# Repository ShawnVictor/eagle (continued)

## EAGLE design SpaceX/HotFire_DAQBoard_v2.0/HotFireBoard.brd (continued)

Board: 2 copper layers, 264 parts (154 on the bottom side), 219 nets, no tracks yet.

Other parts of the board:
C2, C3, C7, C10: 0.1uF; 0805
C5, C6: 47uF; PANASONIC_D
C9: 4.7uF; 0805
CONN1: USB; PN61729
D2: SOD-123
IC1: ATMEGA640-16AI; TQFP100
IC3: 7806DT; TO252
ICSP: FEMALE 2x3; 2X3
LED1: GREEN; CHIPLED_0805
LED2: YELLOW; CHIPLED_0805
LED3: BLUE; CHIPLED_0805
LED4: RED; CHIPLED_0805
R4, R5: 1k; 0805
R6, R7: 10k; 0805
R8, R9: 680; 0805
S1: DTSM-6
U$1: RESONATORSMD; RESONATOR-SMD

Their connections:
ARD_SOL1_WSV_2: IC1.42; also elsewhere on the board
ARD_SOL2_NV_2: IC1.41; also elsewhere on the board
ARD_SOL3_OV_4: IC1.40; also elsewhere on the board
ARD_SOL5: IC1.38; also elsewhere on the board
D0/RX0: IC1.2; also elsewhere on the board
D1/TX0: IC1.3; also elsewhere on the board
D+: CONN1.3; also elsewhere on the board
D-: CONN1.2; also elsewhere on the board
ETHERNET11: IC1.23, R5.2
LOADCELL_1_DOUT: IC1.5; also elsewhere on the board
LOADCELL_1_SCK: IC1.15; also elsewhere on the board
LOADCELL_2_DOUT: IC1.1; also elsewhere on the board
LOADCELL_2_SCK: IC1.16; also elsewhere on the board
LS1: IC1.58; also elsewhere on the board
LS2: IC1.57; also elsewhere on the board
LS3: IC1.56; also elsewhere on the board
LS4: IC1.55; also elsewhere on the board
LS5: IC1.54; also elsewhere on the board
MISO: IC1.22, ICSP.1; also elsewhere on the board
MOSI: IC1.21, ICSP.4; also elsewhere on the board
unnamed: LED1.A, R4.1
unnamed: LED2.A, R5.1
unnamed: LED3.C, R8.1
unnamed 103: R9.2; also elsewhere on the board
unnamed 104: R8.2; also elsewhere on the board
unnamed: LED4.C, R9.1
SCK: IC1.20, ICSP.3; also elsewhere on the board
SCL: IC1.43, R6.1; also elsewhere on the board
SDA: IC1.44, R7.1; also elsewhere on the board
TC1_CS: IC1.71; also elsewhere on the board
TC2_CS: IC1.72; also elsewhere on the board
TC3_CS: IC1.73; also elsewhere on the board
TC4_CS: IC1.74; also elsewhere on the board
TC5_CS: IC1.75; also elsewhere on the board
TC6_CS: IC1.76; also elsewhere on the board
TC7_CS: IC1.77; also elsewhere on the board
TC8_CS: IC1.78; also elsewhere on the board
TC9_CS: IC1.60; also elsewhere on the board
TC10_CS: IC1.59; also elsewhere on the board
TC_DO: IC1.26; also elsewhere on the board
TC_SCK: IC1.25; also elsewhere on the board
VIN: C5.+, IC3.1; also elsewhere on the board
VUSB: C9.2, C10.2, CONN1.1, D2.A
XTAL1: IC1.34; also elsewhere on the board

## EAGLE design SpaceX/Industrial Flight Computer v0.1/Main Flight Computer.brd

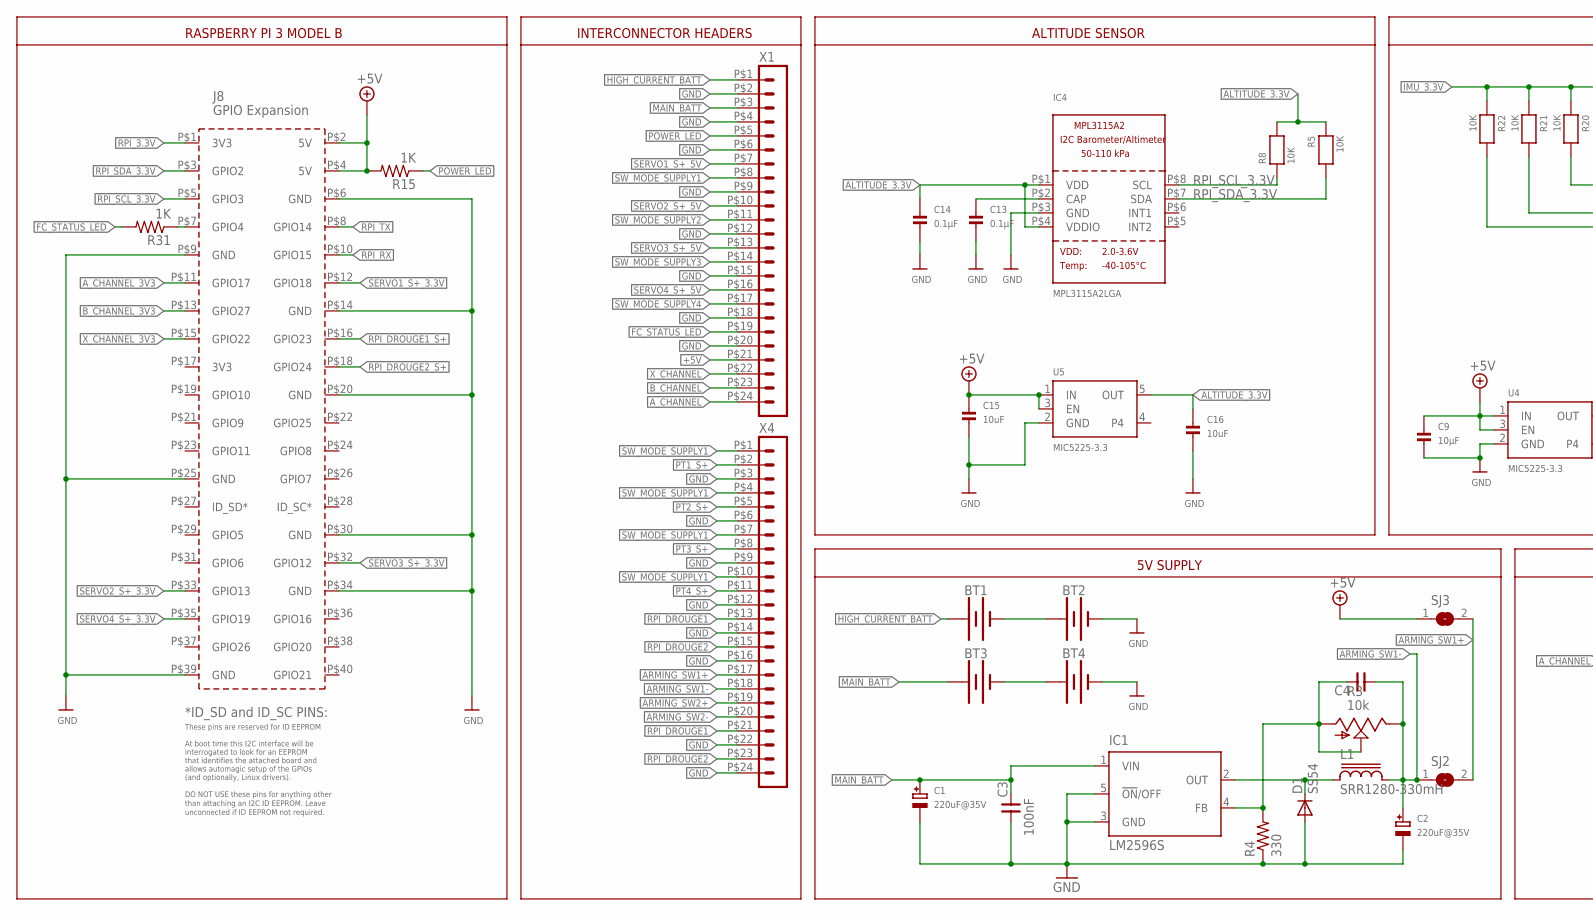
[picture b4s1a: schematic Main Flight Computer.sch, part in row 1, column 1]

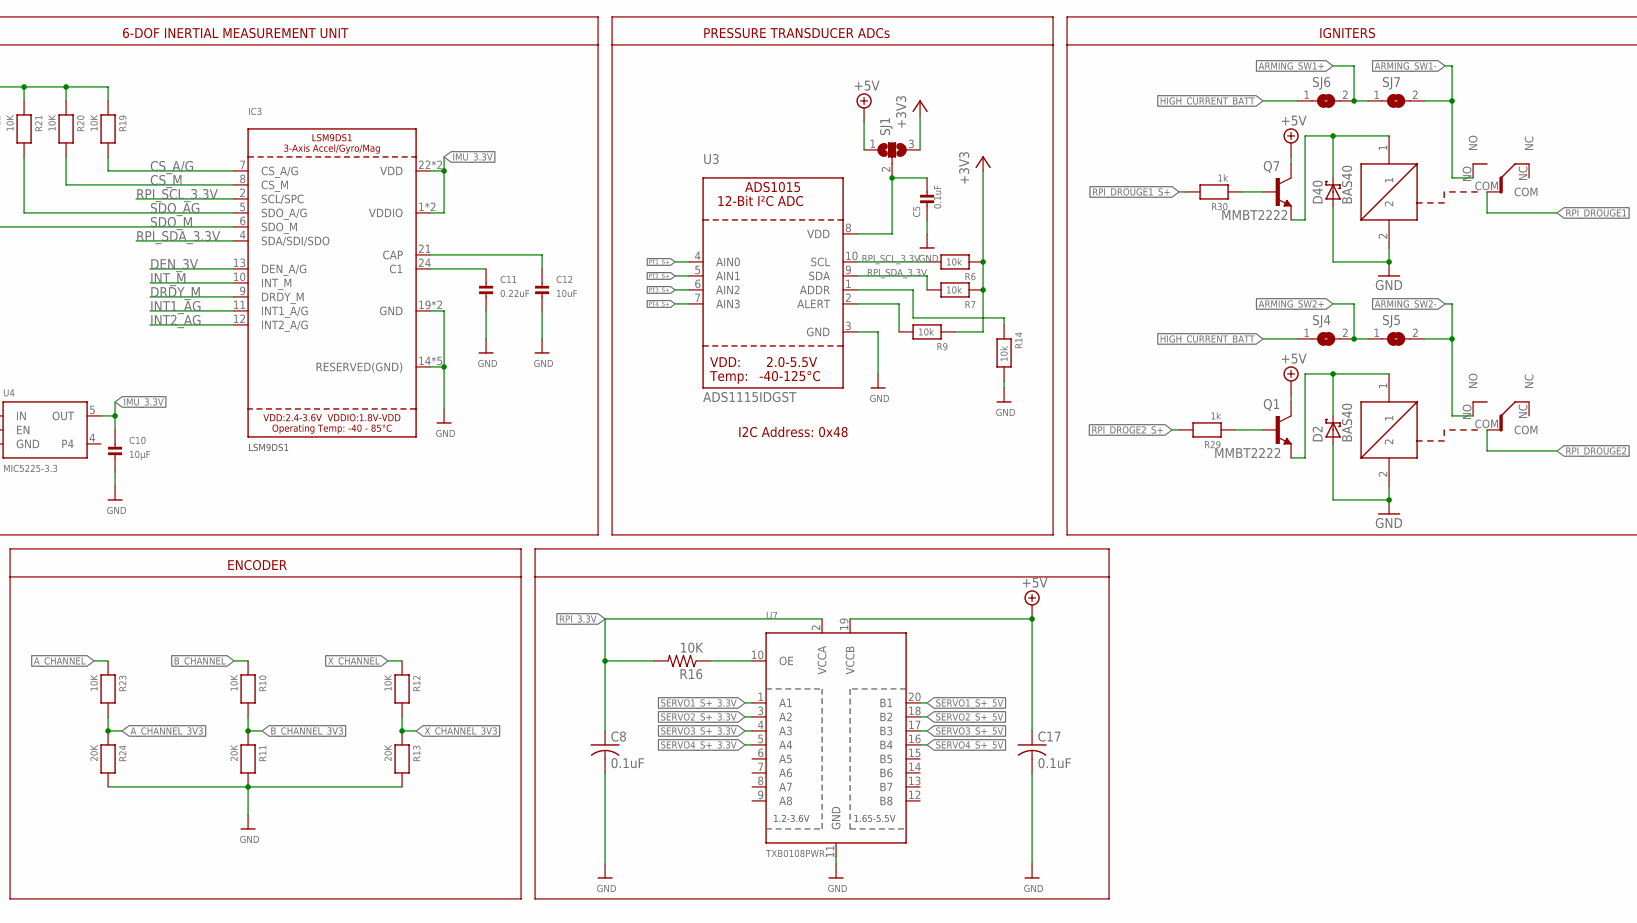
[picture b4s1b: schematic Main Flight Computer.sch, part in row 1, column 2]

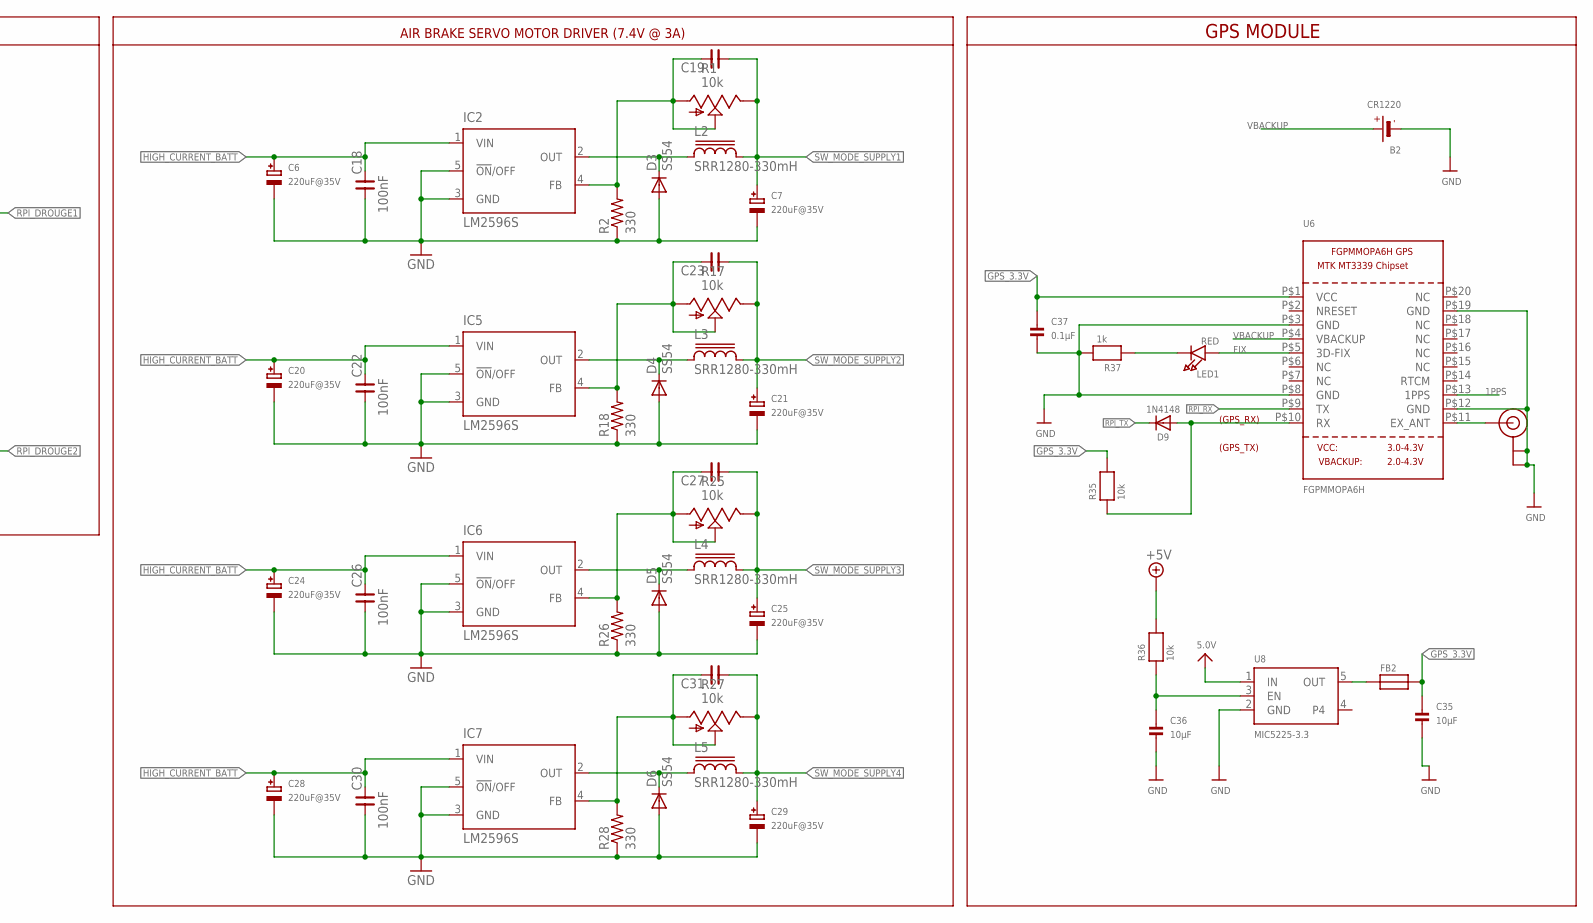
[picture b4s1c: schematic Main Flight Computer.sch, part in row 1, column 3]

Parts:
B2: CR1220
BT1, BT2, BT3, BT4: BATTERY-18650; BATTERY_18650-HOLDER
C1, C2, C6, C7, C20, C21, C24, C25, C28, C29: 220uF@35V; PANASONIC_D
C3, C18, C22, C26, C30: 100nF; 0603
C4, C19, C23, C27, C31: CNP-0603; 0603
C5: 0.1uF; 0805
C8, C17: 0.1uF; C0805
C9, C10, C35, C36: 10µF; 0603
C11: 0.22uF; 0603
C12, C15, C16: 10uF; 0603
C13, C14, C37: 0.1µF; 0603
D1, D3, D4, D5, D6: SS54; DO214AB
D2, D40: BAS40; SOT23
D9: 1N4148; SOD-323
FB2: FERRITE; 0603
IC1, IC2, IC5, IC6, IC7: LM2596S; TO263-5
IC3: LSM9DS1; LGA24_3.5X3.1MM
IC4: MPL3115A2LGA; LGA8
L1, L2, L3, L4, L5: SRR1280-330mH; SRR1280
LED1: RED; CHIPLED_0805
PCB1: RPI3
Q1, Q7: MMBT2222; SOT223
R1, R3, R17, R25, R27: 10k; S64W
R2, R4, R18, R26, R28: 330; R0603
R5, R8, R10, R12, R19, R20, R21, R22, R23: 10K; 0603
R6, R7, R9, R14: 10k; 0805
R11, R13, R24: 20K; 0603
R15, R31: 1K; R0603
R16: 10K; R0805
R29, R30, R37: 1k; 0603
R35, R36: 10k; 0603
SJ1: SJ2W; SJ_2
SJ2, SJ3, SJ4, SJ5, SJ6, SJ7: SJ
U3: ADS1115IDGST; MSOP10
U4, U5, U8: MIC5225-3.3; SOT23-5
U6: FGPMMOPA6H
U7: TXB0108PWR; TSSOP20
U$2: U.FL
U$11, U$13: RW-SH
X1, X4: HEADER_POS24_44914-2401; 44914-2401

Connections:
1PPS: U6.P$13 (1PPS)
5.0V: U8.1 (IN)
+3V3: R6.1, R7.1, R9.1, SJ1.3
+5V: C9.1, C15.1, C17.1, PCB1.P$2 (5V), PCB1.P$4 (5V), Q1.2 (C), Q7.2 (C), R15.2, R36.2, SJ1.1, SJ3.1, U4.1 (IN), U4.3 (EN), U5.1 (IN), U5.3 (EN), U7.19 (VCCB), X1.P$21 (21)
ALTITUDE_3.3V: C14.1, C16.1, IC4.P$1 (VDD), IC4.P$4 (VDDIO), R5.1, R8.2, U5.5 (OUT)
ARMING_SW1+: SJ2.2, SJ3.2, SJ6.2, SJ7.1, X4.P$17 (17)
ARMING_SW1-: C2.+, C4.1, L1.2, R3.E, SJ2.1, SJ7.2, U$11.NO, X4.P$18 (18)
ARMING_SW2+: SJ4.2, SJ5.1, X4.P$19 (19)
ARMING_SW2-: SJ5.2, U$13.NO, X4.P$20 (20)
A_CHANNEL: R23.1, X1.P$24 (24)
A_CHANNEL_3V3: PCB1.P$11 (GPIO17), R23.2, R24.1
B_CHANNEL: R10.1, X1.P$23 (23)
B_CHANNEL_3V3: PCB1.P$13 (GPIO27), R10.2, R11.1
C2: C11.1, IC3.24 (C1)
CAP1: C12.1, IC3.21 (CAP)
CAP2: C13.1, IC4.P$2 (CAP)
CS_A/G: IC3.7 (CS_A/G), R19.2
CS_M: IC3.8 (CS_M), R20.2
DEN_3V: IC3.13 (DEN_A/G)
DRDY_M: IC3.9 (DRDY_M)
FC_STATUS_LED: R31.2, X1.P$19 (19)
FIX: LED1.A, U6.P$5 (3D-FIX)
GND: B2.-, BT2.GND@1 (-), BT4.GND@1 (-), C1.-, C2.-, C3.1, C5.1, C6.-, C7.-, C8.2, C9.2, C10.2, C11.2, C12.2, C13.2, C14.2, C15.2, C16.2, C17.2, C18.1, C20.-, C21.-, C22.1, C24.-, C25.-, C26.1, C28.-, C29.-, C30.1, C35.2, C36.2, C37.2, D1.A, D2.1 (A), D3.A, D4.A, D5.A, D6.A, D40.1 (A), IC1.3 (GND), IC1.5 (!ON!/OFF), IC2.3 (GND), IC2.5 (!ON!/OFF), IC3.14 (RESERVED(GND)), IC3.15 (RESERVED(GND)), IC3.16 (RESERVED(GND)), IC3.17 (RESERVED(GND)), IC3.18 (RESERVED(GND)), IC3.19 (GND), IC3.20 (GND), IC4.P$3 (GND), IC5.3 (GND), IC5.5 (!ON!/OFF), IC6.3 (GND), IC6.5 (!ON!/OFF), IC7.3 (GND), IC7.5 (!ON!/OFF), PCB1.P$6 (GND), PCB1.P$9 (GND), PCB1.P$14 (GND), PCB1.P$20 (GND), PCB1.P$25 (GND), PCB1.P$30 (GND), PCB1.P$34 (GND), PCB1.P$39 (GND), R2.1, R4.1, R11.2, R13.2, R14.2, R18.1, R24.2, R26.1, R28.1, R37.2, U3.3 (GND), U4.2 (GND), U5.2 (GND), U6.P$3 (GND), U6.P$8 (GND), U6.P$12 (GND), U6.P$19 (GND), U7.11 (GND), U8.2 (GND), U$2.P$1 (GND), U$2.P$2 (GND), U$11.2, U$13.2, X1.P$2 (2), X1.P$4 (4), X1.P$6 (6), X1.P$9 (9), X1.P$12 (12), X1.P$15 (15), X1.P$18 (18), X1.P$20 (20), X4.P$3 (3), X4.P$6 (6), X4.P$9 (9), X4.P$12 (12), X4.P$14 (14), X4.P$16 (16), X4.P$22 (22), X4.P$24 (24)
GPS_3.3V: C35.1, C37.1, FB2.2, R35.2, U6.P$1 (VCC)
HIGH_CURRENT_BATT: BT1.PWR@1 (+), C6.+, C18.2, C20.+, C22.2, C24.+, C26.2, C28.+, C30.2, IC2.1 (VIN), IC5.1 (VIN), IC6.1 (VIN), IC7.1 (VIN), SJ4.1, SJ6.1, X1.P$1 (1)
IMU_3.3V: C10.1, IC3.1 (VDDIO), IC3.3 (VDDIO), IC3.22 (VDD), IC3.23 (VDD), R19.1, R20.1, R21.1, R22.1, U4.5 (OUT)
INT1_AG: IC3.11 (INT1_A/G)
INT2_AG: IC3.12 (INT2_A/G)
INT_M: IC3.10 (INT_M)
MAIN_BATT: BT3.PWR@1 (+), C1.+, C3.2, IC1.1 (VIN), X1.P$3 (3)
unnamed: C5.2, SJ1.2, U3.8 (VDD)
unnamed: D4.C, IC5.2 (OUT), L3.1
unnamed: D1.C, IC1.2 (OUT), L1.1
unnamed: C4.2, IC1.4 (FB), R3.A, R3.S, R4.2
unnamed: C23.2, IC5.4 (FB), R17.A, R17.S, R18.2
unnamed: R16.1, U7.10 (OE)
unnamed: D2.3 (C), Q1.3 (E), U$13.1
unnamed: D3.C, IC2.2 (OUT), L2.1
unnamed: C19.2, IC2.4 (FB), R1.A, R1.S, R2.2
unnamed: D5.C, IC6.2 (OUT), L4.1
unnamed: Q1.1 (B), R29.1
unnamed: Q7.1 (B), R30.1
unnamed: PCB1.P$7 (GPIO4), R31.1
unnamed: C27.2, IC6.4 (FB), R25.A, R25.S, R26.2
unnamed: D6.C, IC7.2 (OUT), L5.1
unnamed: C31.2, IC7.4 (FB), R27.A, R27.S, R28.2
unnamed: BT1.GND@1 (-), BT2.PWR@1 (+)
unnamed: U6.P$11 (EX_ANT), U$2.P$3 (SIGNAL)
unnamed: D9.A, R35.1, U6.P$10 (RX)
unnamed: C36.1, R36.1, U8.3 (EN)
unnamed: LED1.C, R37.1
unnamed: R9.2, U3.2 (ALERT)
unnamed: R14.1, U3.1 (ADDR)
unnamed: BT3.GND@1 (-), BT4.PWR@1 (+)
unnamed: D40.3 (C), Q7.3 (E), U$11.1
OUT: FB2.1, U8.5 (OUT)
POWER_LED: R15.1, X1.P$5 (5)
PT1_S+: U3.4 (AIN0), X4.P$2 (2)
PT2_S+: U3.5 (AIN1), X4.P$5 (5)
PT3_S+: U3.6 (AIN2), X4.P$8 (8)
PT4_S+: U3.7 (AIN3), X4.P$11 (11)
RPI_3.3V: C8.1, PCB1.P$1 (3V3), R16.2, U7.2 (VCCA)
RPI_DROGE2_S+: R29.2
RPI_DROUGE1: U$11.COM, X4.P$13 (13), X4.P$21 (21)
RPI_DROUGE1_S+: PCB1.P$16 (GPIO23), R30.2
RPI_DROUGE2: U$13.COM, X4.P$15 (15), X4.P$23 (23)
RPI_DROUGE2_S+: PCB1.P$18 (GPIO24)
RPI_RX: PCB1.P$10 (GPIO15), U6.P$9 (TX)
RPI_SCL_3.3V: IC3.2 (SCL/SPC), IC4.P$8 (SCL), PCB1.P$5 (GPIO3), R6.2, R8.1, U3.10 (SCL)
RPI_SDA_3.3V: IC3.4 (SDA/SDI/SDO), IC4.P$7 (SDA), PCB1.P$3 (GPIO2), R5.2, R7.2, U3.9 (SDA)
RPI_TX: D9.C, PCB1.P$8 (GPIO14)
SDO_AG: IC3.5 (SDO_A/G), R21.2
SDO_M: IC3.6 (SDO_M), R22.2
SERVO1_S+_3.3V: PCB1.P$12 (GPIO18), U7.1 (A1)
SERVO1_S+_5V: U7.20 (B1), X1.P$7 (7)
SERVO2_S+_3.3V: PCB1.P$33 (GPIO13), U7.3 (A2)
SERVO2_S+_5V: U7.18 (B2), X1.P$10 (10)
SERVO3_S+_3.3V: PCB1.P$32 (GPIO12), U7.4 (A3)
SERVO3_S+_5V: U7.17 (B3), X1.P$13 (13)
SERVO4_S+_3.3V: PCB1.P$35 (GPIO19), U7.5 (A4)
SERVO4_S+_5V: U7.16 (B4), X1.P$16 (16)
SW_MODE_SUPPLY1: C7.+, C19.1, L2.2, R1.E, X1.P$8 (8), X4.P$1 (1), X4.P$4 (4), X4.P$7 (7), X4.P$10 (10)
SW_MODE_SUPPLY2: C21.+, C23.1, L3.2, R17.E, X1.P$11 (11)
SW_MODE_SUPPLY3: C25.+, C27.1, L4.2, R25.E, X1.P$14 (14)
SW_MODE_SUPPLY4: C29.+, C31.1, L5.2, R27.E, X1.P$17 (17)
VBACKUP: B2.+$1 (+), B2.+$2 (+), U6.P$4 (VBACKUP)
X_CHANNEL: R12.1, X1.P$22 (22)
X_CHANNEL_3V3: PCB1.P$15 (GPIO22), R12.2, R13.1

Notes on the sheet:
RASPBERRY PI 3 MODEL B
INTERCONNECTOR HEADERS
ALTITUDE SENSOR
6-DOF INERTIAL MEASUREMENT UNIT
5V SUPPLY
ENCODER
IGNITERS
I2C Address: 0x48
PRESSURE TRANSDUCER ADCs
AIR BRAKE SERVO MOTOR DRIVER (7.4V @ 3A)
(GPS_RX)
(GPS_TX)
GPS MODULE

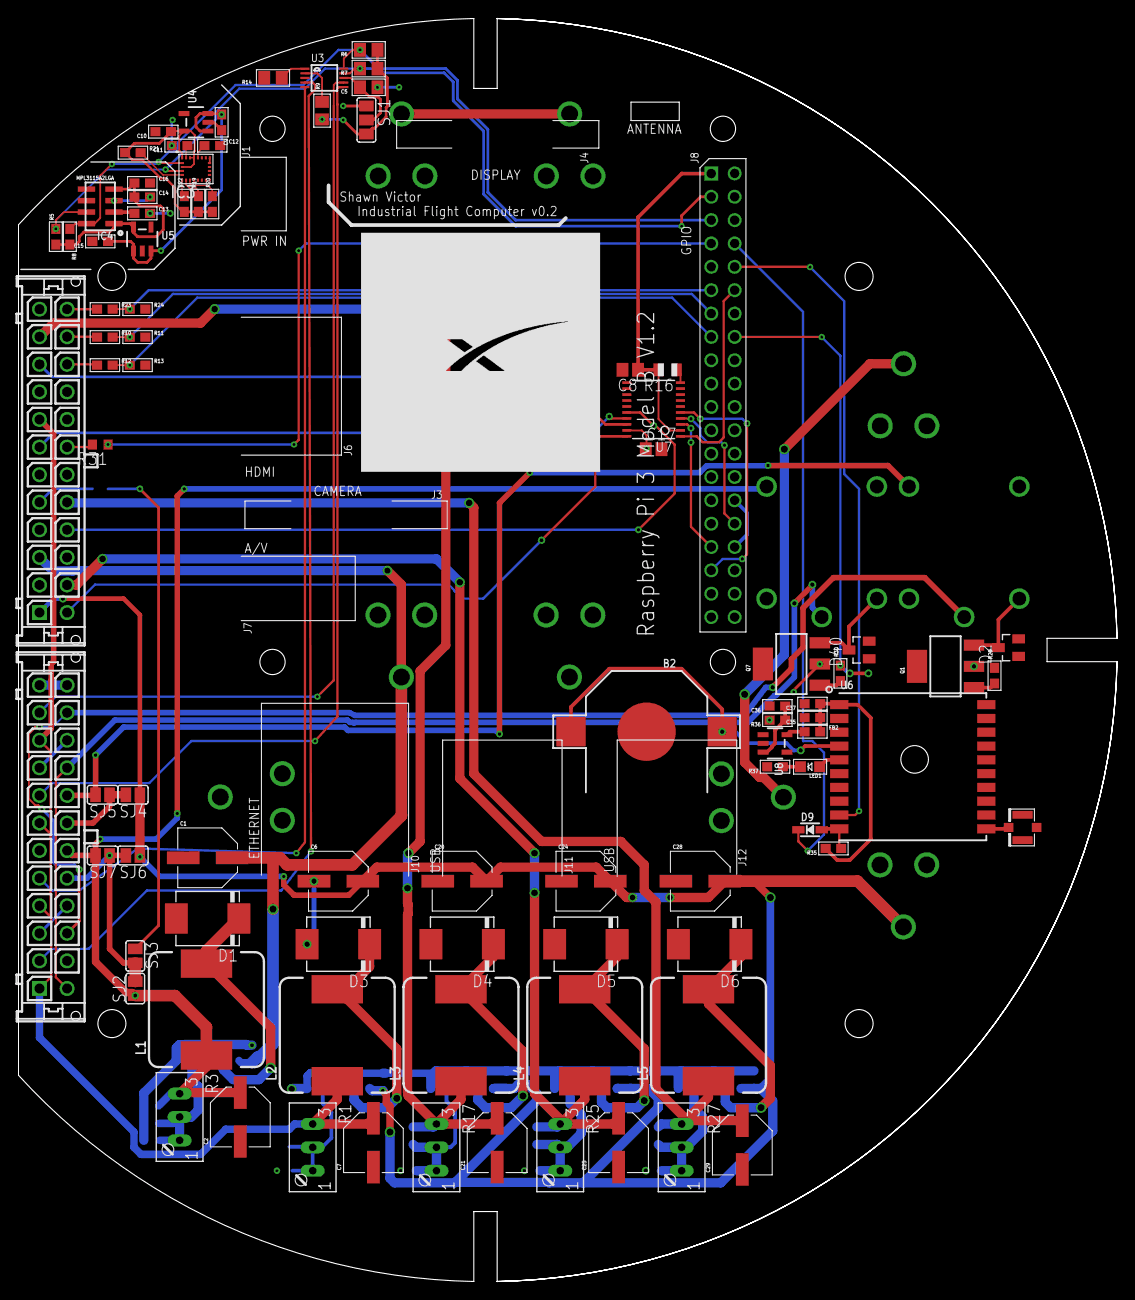
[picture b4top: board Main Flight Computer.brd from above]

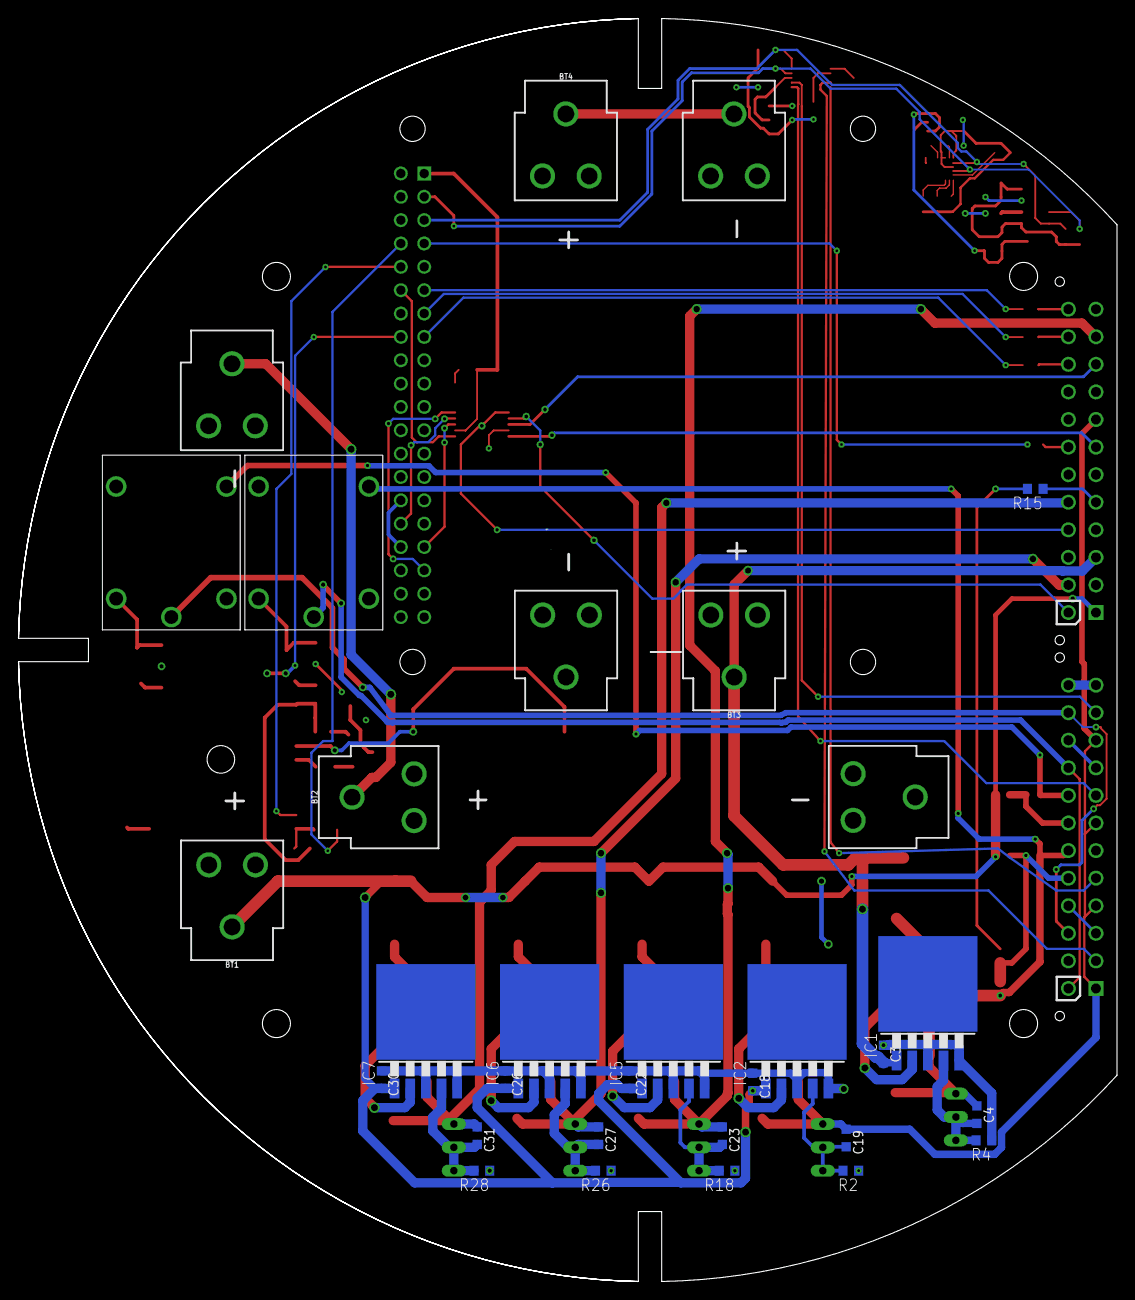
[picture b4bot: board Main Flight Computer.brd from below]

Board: 2 copper layers, 119.5 x 137.4 mm, 116 parts (27 on the bottom side), 79 nets.

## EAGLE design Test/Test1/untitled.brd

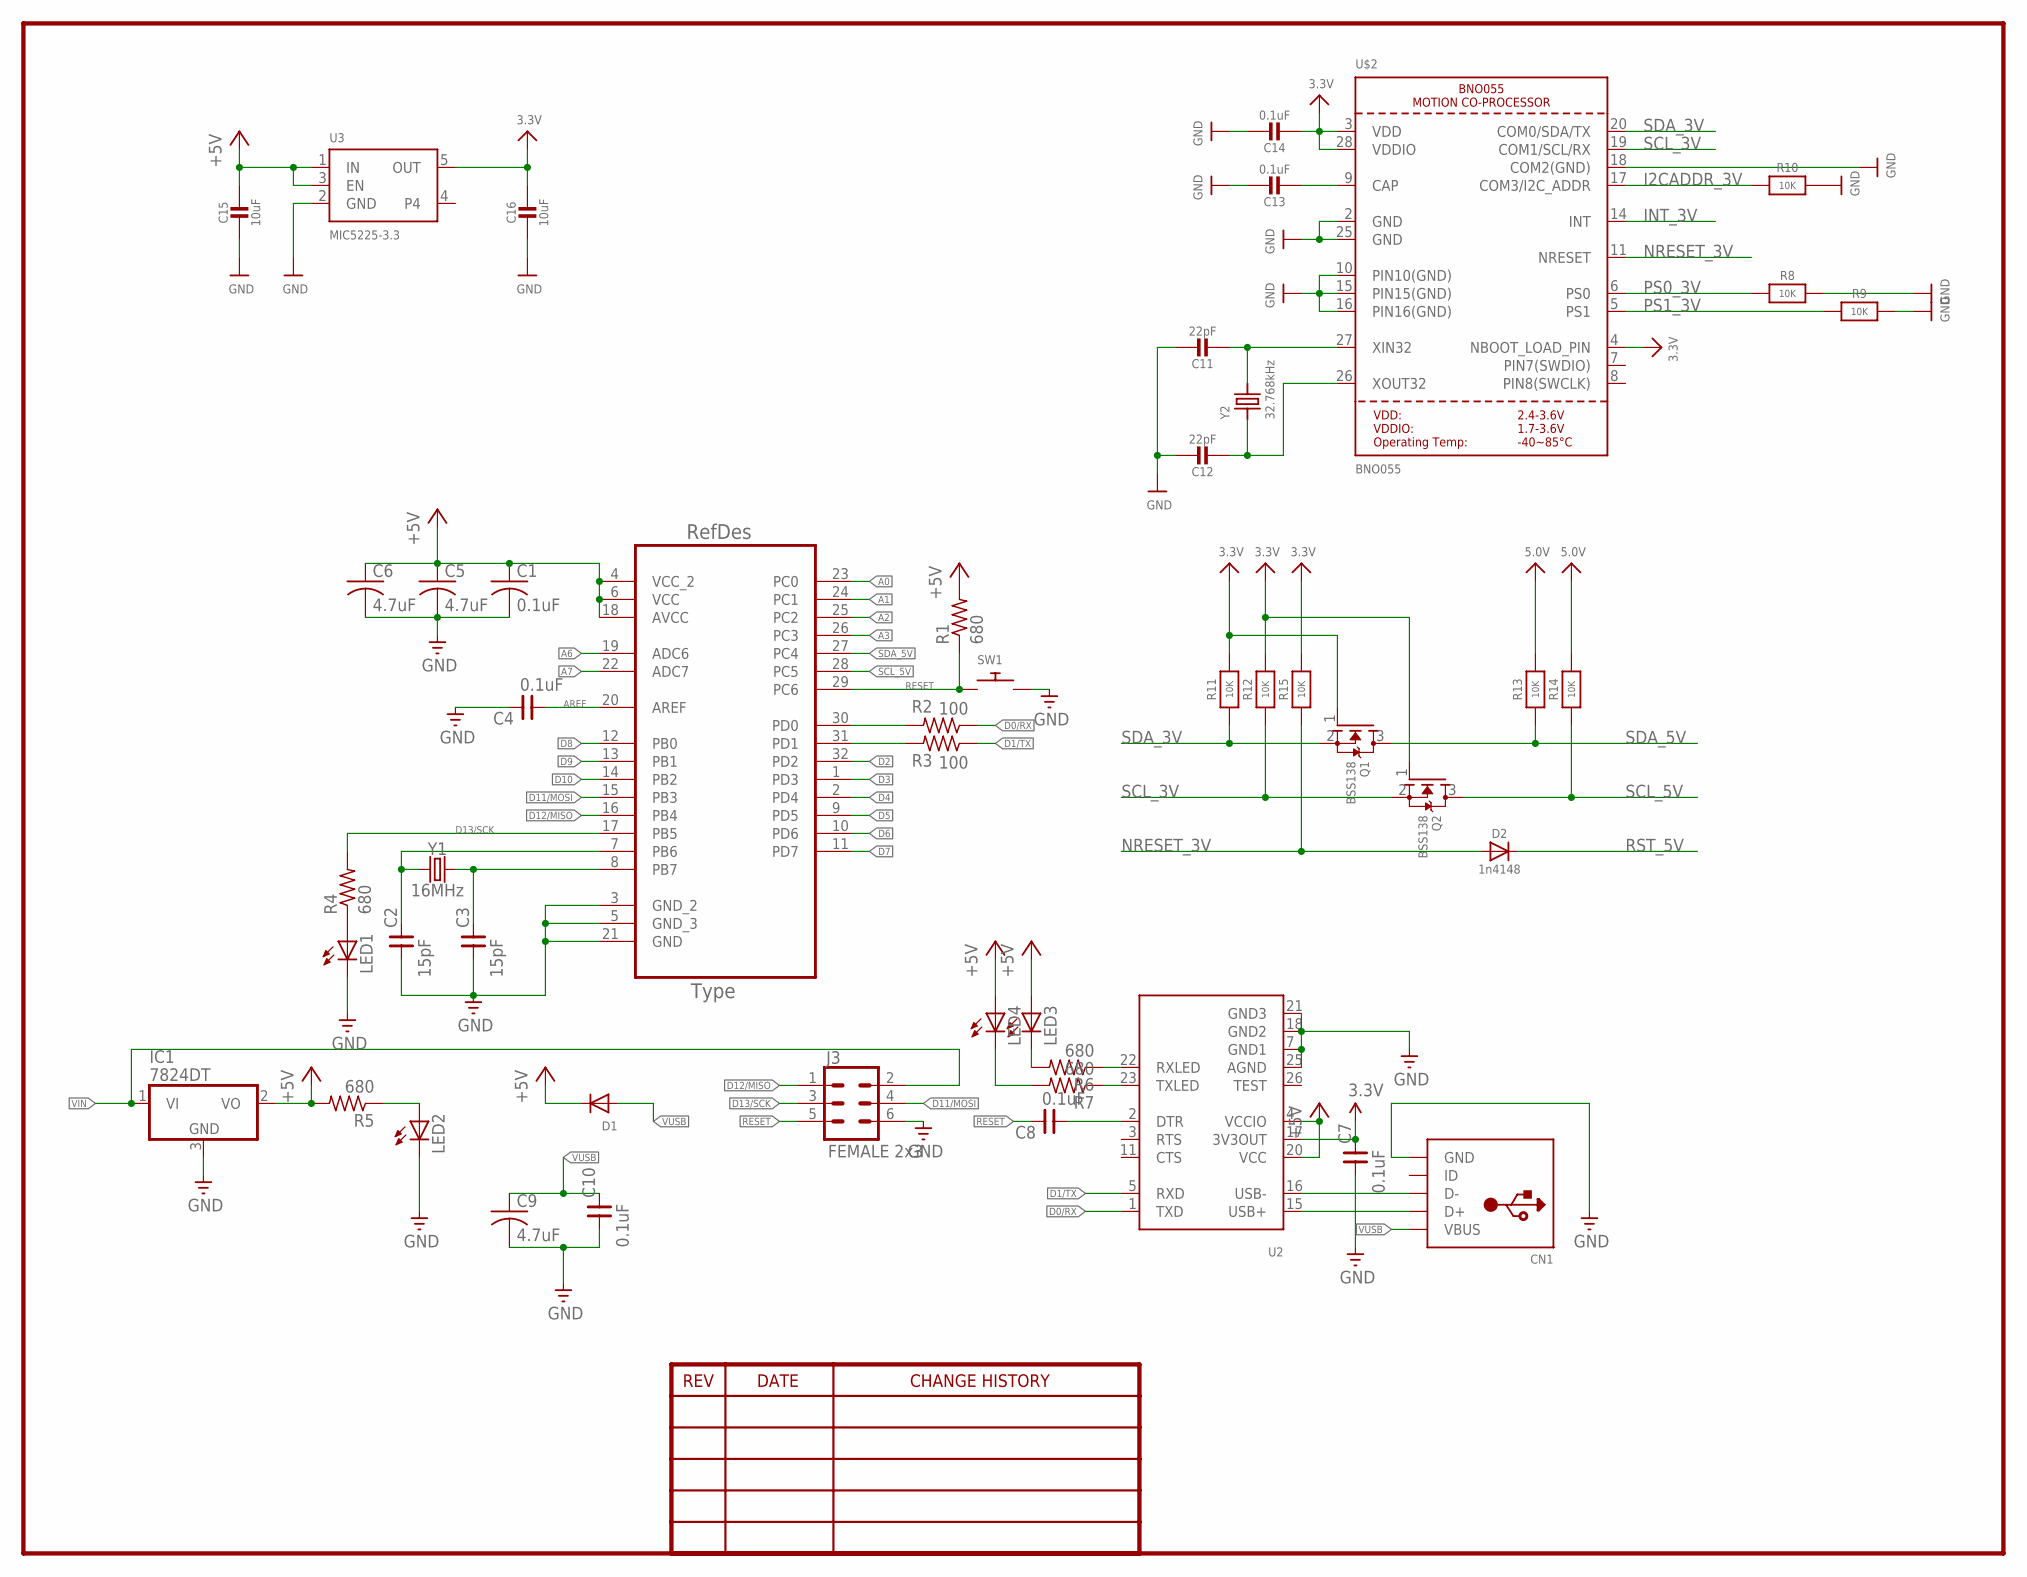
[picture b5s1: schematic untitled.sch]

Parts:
C1: 0.1uF; C0805
C2, C3: 15pF; 0805
C4, C7, C8, C10: 0.1uF; 0805
C5, C6, C9: 4.7uF; C0805
C11, C12: 22pF; 0805-NO
C13: 0.1uF; 0805-NO
C14: 0.1uF; 0805_10MGAP
C15: 10uF; 0805-NO
C16: 10uF; 0805_10MGAP
CN1: USBMINIB; USB-MINIB
D1: DIODESOD-123; SOD-123
D2: 1n4148; SOD-323
IC1: 7824DT; TO252
J3: FEMALE 2x3; 2X3
LED1, LED2, LED3, LED4: LEDCHIPLED_0805; CHIPLED_0805
Q1, Q2: BSS138; SOT23-WIDE
R1, R4, R5, R6, R7: 680; R0805
R2, R3: 100; R0805
R8, R9, R10, R11, R12, R15: 10K; 0805-NO
R13, R14: 10K; _0805MP
SW1: SWITCH_PUSHBUTTONEVQ-PE; TACT_PANA-EVQ
U1: ATMEGA328P-AU; QFP80P900X900X120-32N
U2: FT232RLSSOP28; SSOP28DB
U3: MIC5225-3.3; SOT23-5
U$2: BNO055
Y1: 16MHz; HC49US
Y2: 32.768kHz; CRYSTAL_8X3.8

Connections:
3.3V: C7.2, C14.2, C16.1, Q1.1 (G), Q2.1 (G), R11.2, R12.2, R15.2, U2.17 (3V3OUT), U3.5 (OUT), U$2.3 (VDD), U$2.4 (NBOOT_LOAD_PIN), U$2.28 (VDDIO)
5.0V: R13.2, R14.2
+5V: C1.1, C5.1, C6.1, C15.1, D1.C, IC1.2 (VO), LED3.A, LED4.A, R5.2, U1.4 (VCC_2), U1.6 (VCC), U1.18 (AVCC), U2.4 (VCCIO), U2.20 (VCC), U3.1 (IN), U3.3 (EN)
A0: U1.23 (PC0)
A1: U1.24 (PC1)
A2: U1.25 (PC2)
A3: U1.26 (PC3)
A6: U1.19 (ADC6)
A7: U1.22 (ADC7)
AREF: C4.1, U1.20 (AREF)
D0/RX: R2.1, U2.1 (TXD)
D1/TX: R3.1, U2.5 (RXD)
D2: U1.32 (PD2)
D3: U1.1 (PD3)
D4: U1.2 (PD4)
D5: U1.9 (PD5)
D6: U1.10 (PD6)
D7: U1.11 (PD7)
D8: U1.12 (PB0)
D9: U1.13 (PB1)
D10: U1.14 (PB2)
D11/MOSI: J3.4, U1.15 (PB3)
D12/MISO: J3.1, U1.16 (PB4)
D13/SCK: J3.3, R4.2, U1.17 (PB5)
GND: C1.2, C2.1, C3.1, C4.2, C5.2, C6.2, C7.1, C9.2, C10.1, C11.1, C12.1, C13.1, C14.1, C15.2, C16.2, CN1.GND, IC1.3 (GND), J3.6, LED1.C, LED2.C, R8.2, R9.2, R10.2, SW1.P$2, U1.3 (GND_2), U1.5 (GND_3), U1.21 (GND), U2.7 (GND1), U2.18 (GND2), U2.21 (GND3), U2.25 (AGND), U3.2 (GND), U$2.2 (GND), U$2.10 (PIN10(GND)), U$2.15 (PIN15(GND)), U$2.16 (PIN16(GND)), U$2.18 (COM2(GND)), U$2.25 (GND)
I2CADDR_3V: R10.1, U$2.17 (COM3/I2C_ADDR)
INT_3V: U$2.14 (INT)
unnamed: C3.2, U1.8 (PB7), Y1.2
unnamed: C2.2, U1.7 (PB6), Y1.1
unnamed: LED2.A, R5.1
unnamed: CN1.D+, U2.15 (USB+)
unnamed: CN1.D-, U2.16 (USB-)
unnamed: R2.2, U1.30 (PD0)
unnamed: R3.2, U1.31 (PD1)
unnamed: LED3.C, R6.2
unnamed: C11.2, U$2.27 (XIN32), Y2.P$4 (2)
unnamed: C12.2, U$2.26 (XOUT32), Y2.P$1 (1)
unnamed: R6.1, U2.22 (RXLED)
unnamed: R7.1, U2.23 (TXLED)
unnamed: C8.1, U2.2 (DTR)
unnamed: LED4.C, R7.2
unnamed: C13.2, U$2.9 (CAP)
NRESET_3V: D2.A, R15.1, U$2.11 (NRESET)
PS0_3V: R8.1, U$2.6 (PS0)
PS1_3V: R9.1, U$2.5 (PS1)
RESET: C8.2, J3.5, R1.1, SW1.P$1, U1.29 (PC6)
RST_5V: D2.C
SCL_3V: Q2.2 (S), R12.1, U$2.19 (COM1/SCL/RX)
SCL_5V: Q2.3 (D), R14.1, U1.28 (PC5)
SDA_3V: Q1.2 (S), R11.1, U$2.20 (COM0/SDA/TX)
SDA_5V: Q1.3 (D), R13.1, U1.27 (PC4)
VIN: IC1.1 (VI), J3.2
VUSB: C9.1, C10.2, CN1.VBUS, D1.A

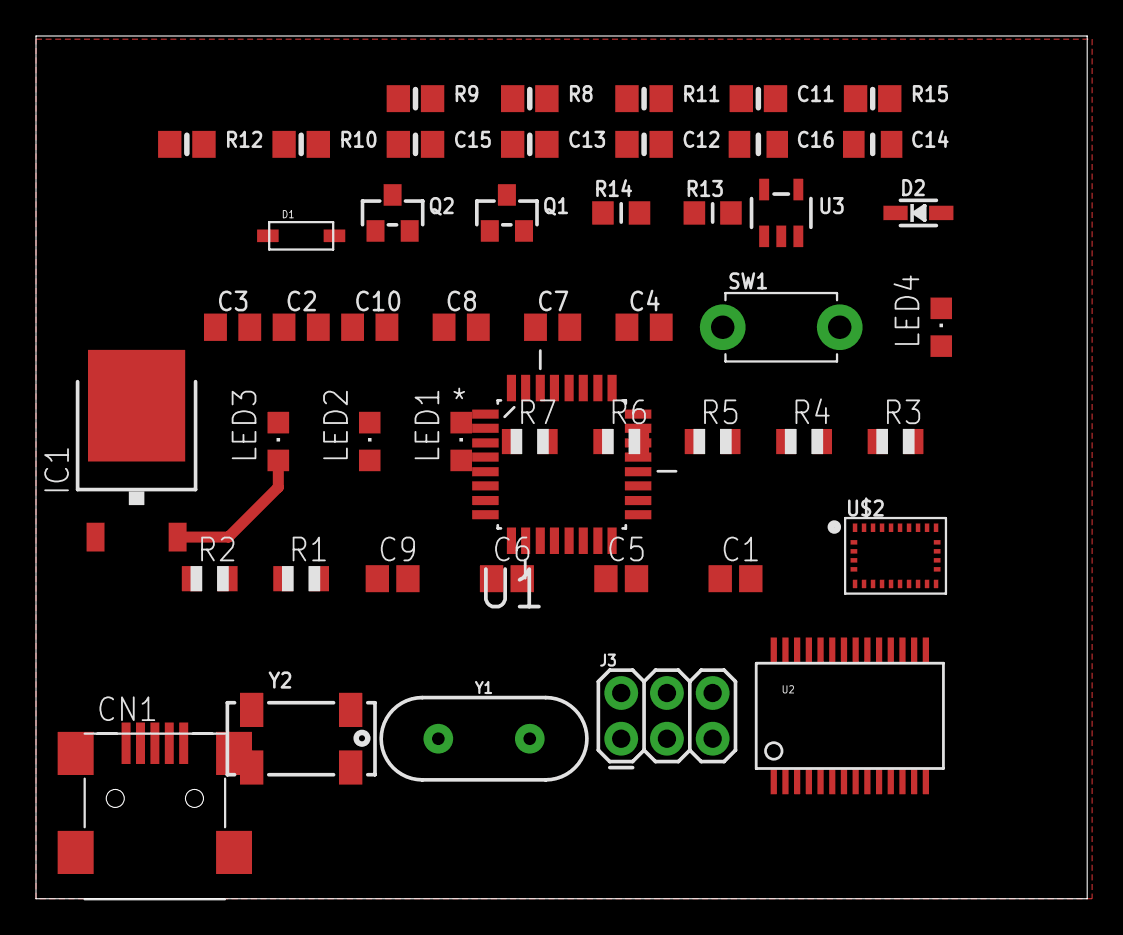
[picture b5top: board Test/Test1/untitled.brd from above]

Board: 2 copper layers, 58.4 x 47.9 mm, 49 parts (0 on the bottom side), 36 nets.

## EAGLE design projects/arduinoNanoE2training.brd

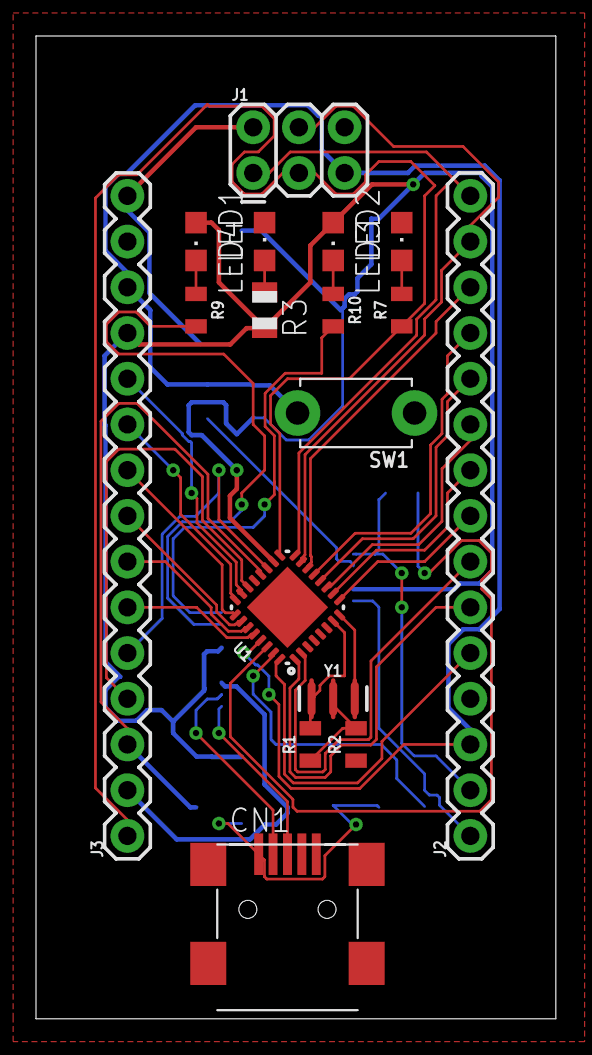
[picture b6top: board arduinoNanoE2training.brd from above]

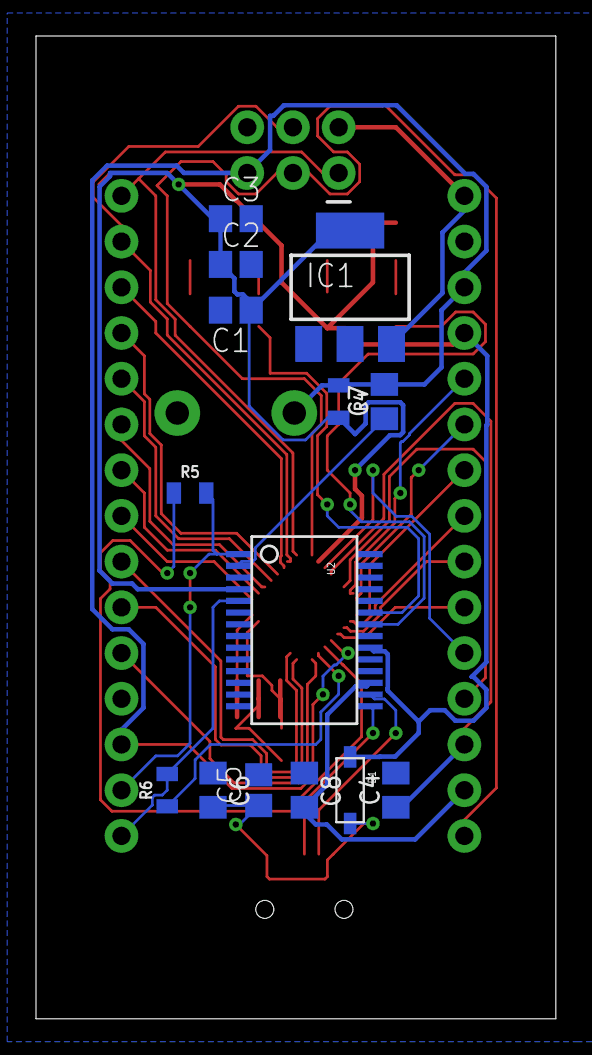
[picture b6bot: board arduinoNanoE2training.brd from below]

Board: 2 copper layers, 28.9 x 54.6 mm, 31 parts (14 on the bottom side), 43 nets.

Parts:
C1, C2, C5: 4.7uF; C0805
C3: 0.1uF; C0805
C4, C6, C7, C8: 0.1uF; 0805
CN1: USB-MINIB
D1: SOD-123
IC1: LM317MSTT3; SOT223
J1: FEMALE 2x3; 2X3
J2, J3: 1X15
LED1, LED2, LED3, LED4: CHIPLED_0805
R1: 1M; 0805
R2: 27; 0805
R3: 680; R0805
R4, R7, R9, R10: 680; 0805
R5, R6: 100; 0805
SW1: TACT_PANA-EVQ
U1: MLF32-PAD
U2: SSOP28DB
Y1: 16MHz; RESONATOR-SMD-3.2X1.3

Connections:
3.3V: C8.2, J3.2, U2.17
+5V: C1.1, C2.1, C3.1, D1.C, IC1.4, J3.12, LED3.A, LED4.A, R3.2, R4.2, U1.4, U1.6, U1.18, U2.4, U2.20
A0: J3.11, U1.23
A1: J3.10, U1.24
A2: J3.9, U1.25
A3: J3.8, U1.26
A4: J3.7, U1.27
A5: J3.6, U1.28
A6: J3.5, U1.19
A7: J3.4, U1.22
AREF: C4.1, J3.3, U1.20
D0/RX: J2.2, R5.2, U2.1
D1/TX: J2.1, R6.2, U2.5
D2: J2.5, U1.32
D3: J2.6, U1.1
D4: J2.7, U1.2
D5: J2.8, U1.9
D6: J2.9, U1.10
D7: J2.10, U1.11
D8: J2.11, U1.12
D9: J2.12, U1.13
D10: J2.13, U1.14
D11/MOSI: J1.4, J2.14, U1.15
D12/MISO: J1.1, J2.15, U1.16
D13/SCK: J1.3, J3.1, R7.1, U1.17
GND: C1.2, C2.2, C3.2, C4.2, C5.2, C6.1, C8.1, CN1.GND, IC1.1, J1.6, J2.4, J3.14, LED1.C, LED2.C, R2.1, SW1.P$1, U1.3, U1.5, U1.21, U1.PAD, U2.7, U2.18, U2.21, U2.25
unnamed: LED3.C, R10.1
unnamed: LED4.C, R9.1
unnamed: LED1.A, R3.1
unnamed: R9.2, U2.22
unnamed: R10.2, U2.23
unnamed: C7.1, U2.2
unnamed: R1.2, U1.7, Y1.1
unnamed: U1.8, Y1.3
unnamed: R1.1, R2.2, Y1.2
unnamed: CN1.D-, U2.16
unnamed: CN1.D+, U2.15
unnamed: R5.1, U1.30
unnamed: R6.1, U1.31
unnamed: LED2.A, R7.2
RESET: C7.2, J1.5, J2.3, J3.13, R4.1, SW1.P$2, U1.29
VIN: IC1.3, J1.2, J3.15
VUSB: C5.1, C6.2, CN1.VBUS, D1.A
